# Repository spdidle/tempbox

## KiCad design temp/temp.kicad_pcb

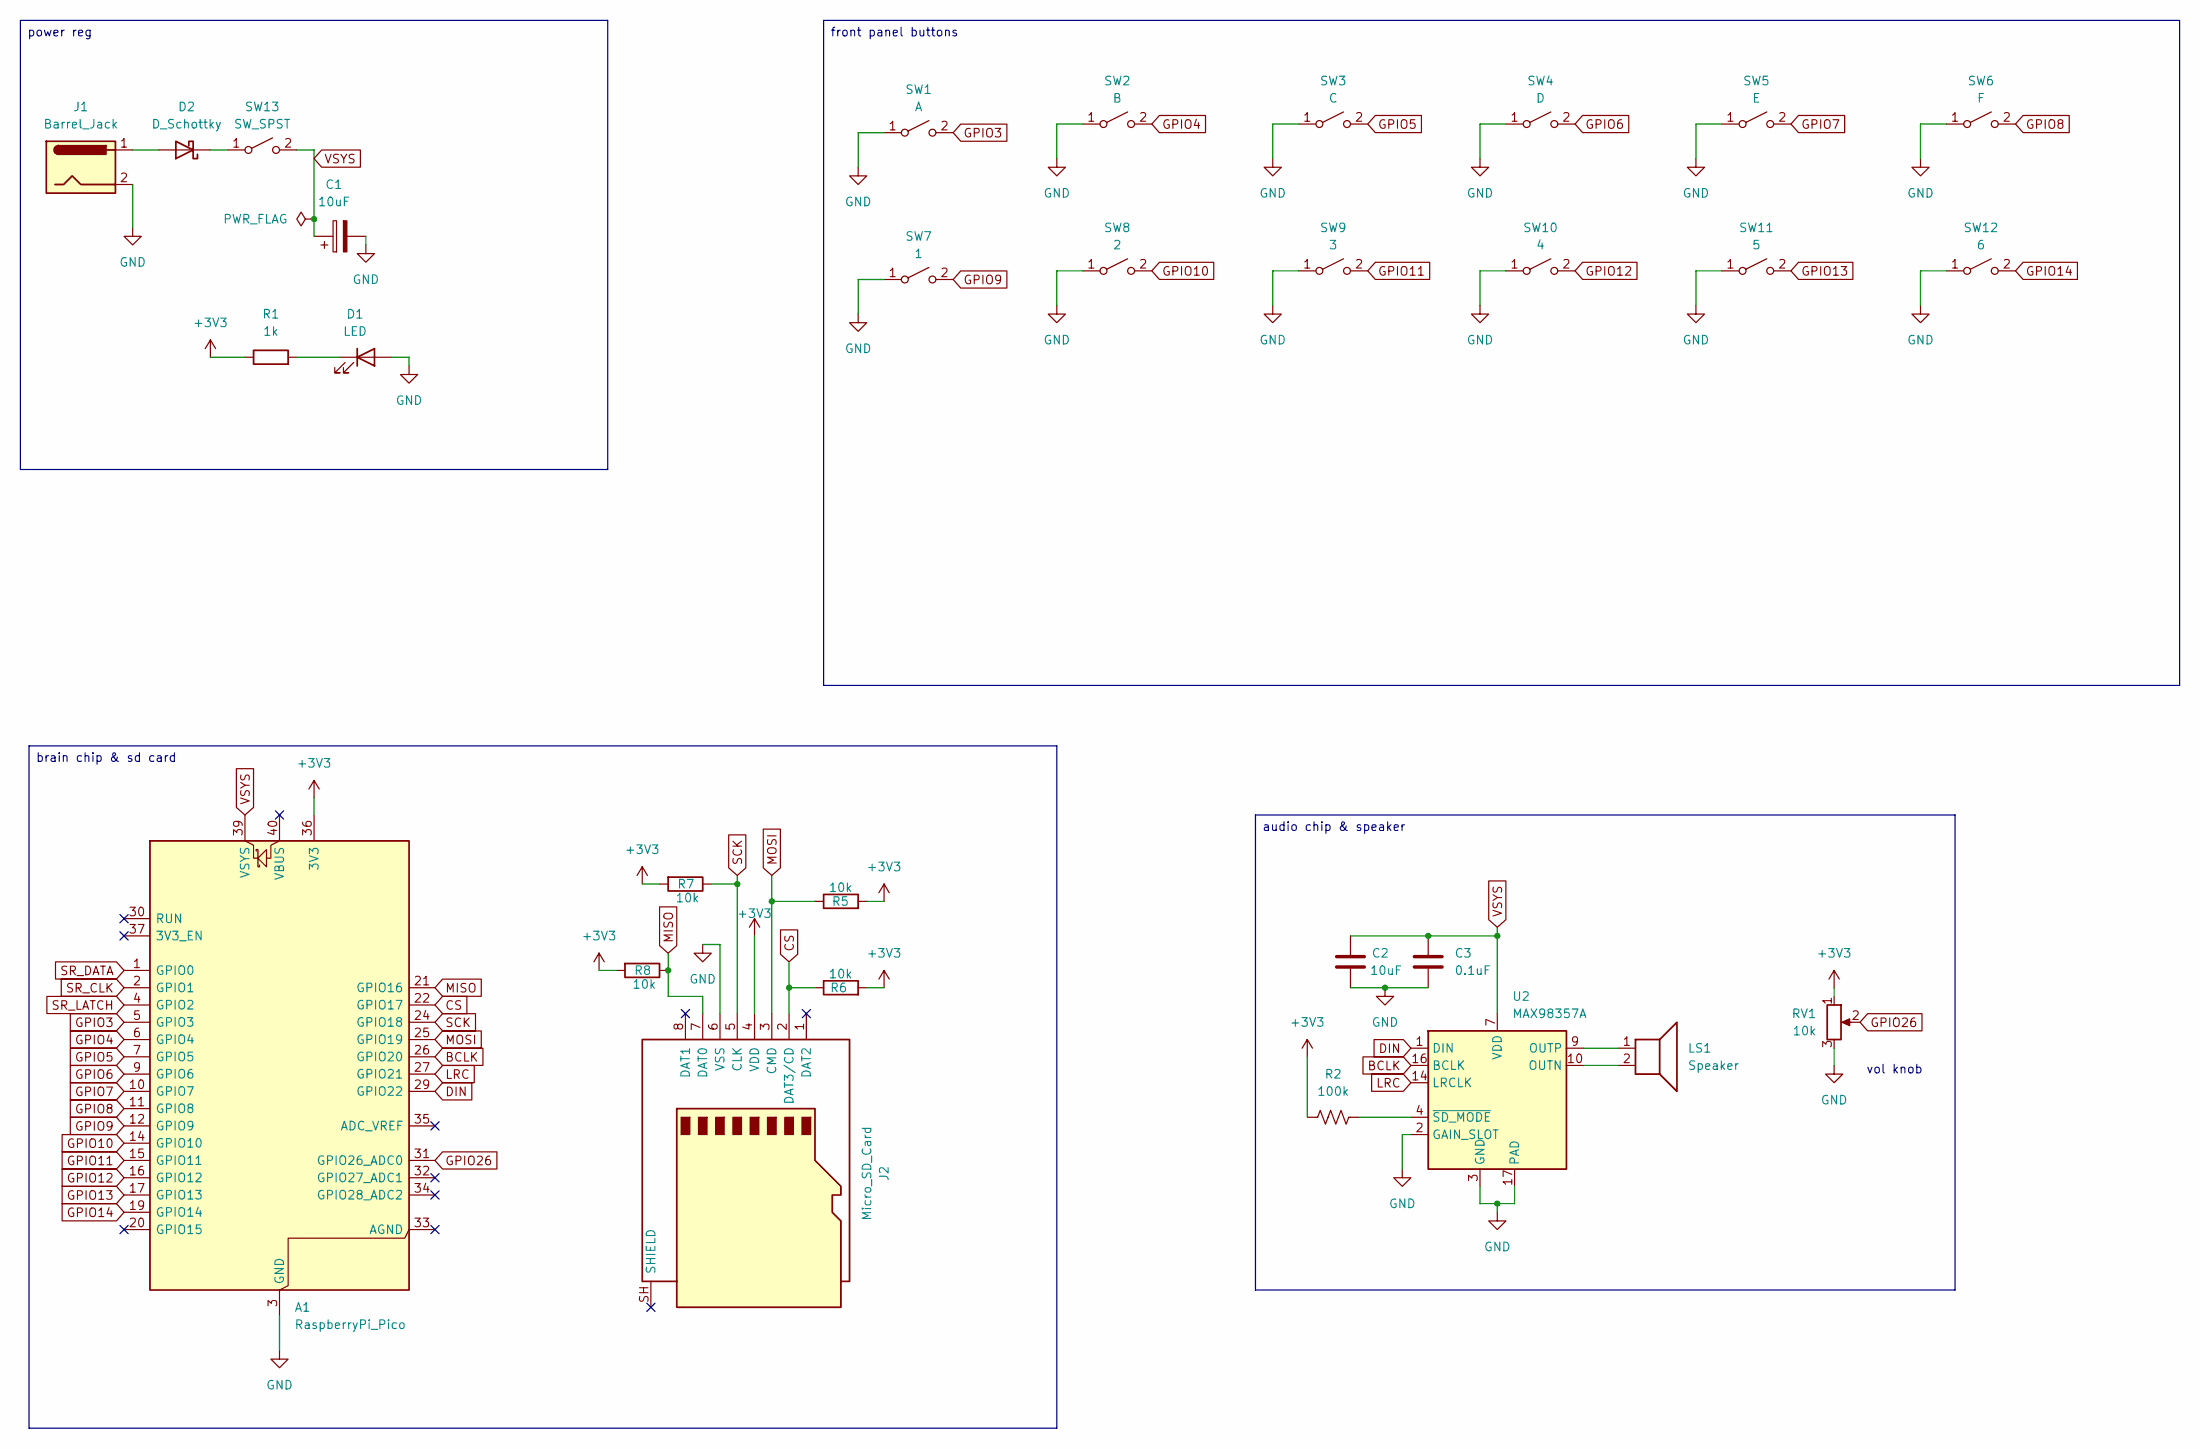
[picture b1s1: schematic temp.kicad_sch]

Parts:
A1: RaspberryPi_Pico; RaspberryPi_Pico_Common_Unspecified
C1, C2: 10uF; CP_Radial_D5.0mm_P2.00mm
C3: 0.1uF; CP_Radial_D5.0mm_P2.00mm
D1: LED; LED_D10.0mm
D2: D_Schottky; D_3220_8050Metric_Pad2.65x5.15mm_HandSolder
J1: Barrel_Jack; BarrelJack_Horizontal
J2: Micro_SD_Card; microSD_HC_Wuerth_693072010801
LS1: Speaker; PinHeader_1x02_P2.54mm_Vertical
R1: 1k; R_Axial_DIN0207_L6.3mm_D2.5mm_P2.54mm_Vertical
R2: 100k; R_Axial_DIN0207_L6.3mm_D2.5mm_P2.54mm_Vertical
R5, R6, R7, R8: 10k; R_Axial_DIN0207_L6.3mm_D2.5mm_P2.54mm_Vertical
RV1: 10k; Potentiometer_Alps_RK09L_Single_Horizontal
SW1: A; SW_PUSH-12mm
SW2: B; SW_PUSH-12mm
SW3: C; SW_PUSH-12mm
SW4: D; SW_PUSH-12mm
SW5: E; SW_PUSH-12mm
SW6: F; SW_PUSH-12mm
SW7: 1; SW_PUSH-12mm
SW8: 2; SW_PUSH-12mm
SW9: 3; SW_PUSH-12mm
SW10: 4; SW_PUSH-12mm
SW11: 5; SW_PUSH-12mm
SW12: 6; SW_PUSH-12mm
SW13: SW_SPST; SW_Slide-03_Wuerth-WS-SLTV_10x2.5x6.4_P2.54mm
U2: MAX98357A; TQFN-16-1EP_3x3mm_P0.5mm_EP1.23x1.23mm

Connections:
+3V3: A1.36 (3V3), J2.4 (VDD), R1.1, R2.1, R5.2, R6.2, R7.2, R8.2, RV1.1
BCLK: A1.26 (GPIO20), U2.16 (BCLK)
CS: A1.22 (GPIO17), J2.2 (DAT3/CD), R6.1
DIN: A1.29 (GPIO22), U2.1 (DIN)
GND: A1.3 (GND), A1.8 (GND), A1.13 (GND), A1.18 (GND), A1.23 (GND), A1.28 (GND), A1.38 (GND), C1.2, C2.2, C3.2, D1.2 (A), J1.2, J2.6 (VSS), RV1.3, SW1.1 (A), SW2.1 (A), SW3.1 (A), SW4.1 (A), SW5.1 (A), SW6.1 (A), SW7.1 (A), SW8.1 (A), SW9.1 (A), SW10.1 (A), SW11.1 (A), SW12.1 (A), U2.2 (GAIN_SLOT), U2.3 (GND), U2.11 (GND), U2.15 (GND), U2.17 (PAD)
GPIO3: A1.5 (GPIO3), SW1.2 (B)
GPIO4: A1.6 (GPIO4), SW2.2 (B)
GPIO5: A1.7 (GPIO5), SW3.2 (B)
GPIO6: A1.9 (GPIO6), SW4.2 (B)
GPIO7: A1.10 (GPIO7), SW5.2 (B)
GPIO8: A1.11 (GPIO8), SW6.2 (B)
GPIO9: A1.12 (GPIO9), SW7.2 (B)
GPIO10: A1.14 (GPIO10), SW8.2 (B)
GPIO11: A1.15 (GPIO11), SW9.2 (B)
GPIO12: A1.16 (GPIO12), SW10.2 (B)
GPIO13: A1.17 (GPIO13), SW11.2 (B)
GPIO14: A1.19 (GPIO14), SW12.2 (B)
GPIO26: A1.31 (GPIO26_ADC0), RV1.2
LRC: A1.27 (GPIO21), U2.14 (LRCLK)
MISO: A1.21 (GPIO16), J2.7 (DAT0), R8.1
MOSI: A1.25 (GPIO19), J2.3 (CMD), R5.1
unnamed: D1.1 (K), R1.2
unnamed: D2.2 (A), J1.1
unnamed: D2.1 (K), SW13.1 (A)
unnamed: LS1.2, U2.10 (OUTN)
unnamed: LS1.1, U2.9 (OUTP)
unnamed: R2.2, U2.4 (~SD_MODE)
SCK: A1.24 (GPIO18), J2.5 (CLK), R7.1
SR_CLK: A1.2 (GPIO1)
SR_DATA: A1.1 (GPIO0)
SR_LATCH: A1.4 (GPIO2)
VSYS: A1.39 (VSYS), C1.1, C2.1, C3.1, SW13.2 (B), U2.7 (VDD), U2.8 (VDD)

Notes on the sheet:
vol knob
brain chip & sd card
front panel buttons
power reg
audio chip & speaker

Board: 2 copper layers, 30 parts (0 on the bottom side), 29 nets, no tracks yet.
